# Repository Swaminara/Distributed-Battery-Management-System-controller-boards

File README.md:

# Distributed-Battery-Management-System-controller-boards

This repository contains the hardware design files of the cell-level controller boards of a distributed Battery Management System.

The boards are designed using Easily Applicable Graphical Layout Editor (EAGLE) 7.1.0 for Windows. However, they can be viewed and edited using other versions also. 

A journal paper explaining the individual modules of the cell-level controller is under review and will be soon updated to this repository. 

This repository is protected under the MIT license as attached in the repository.

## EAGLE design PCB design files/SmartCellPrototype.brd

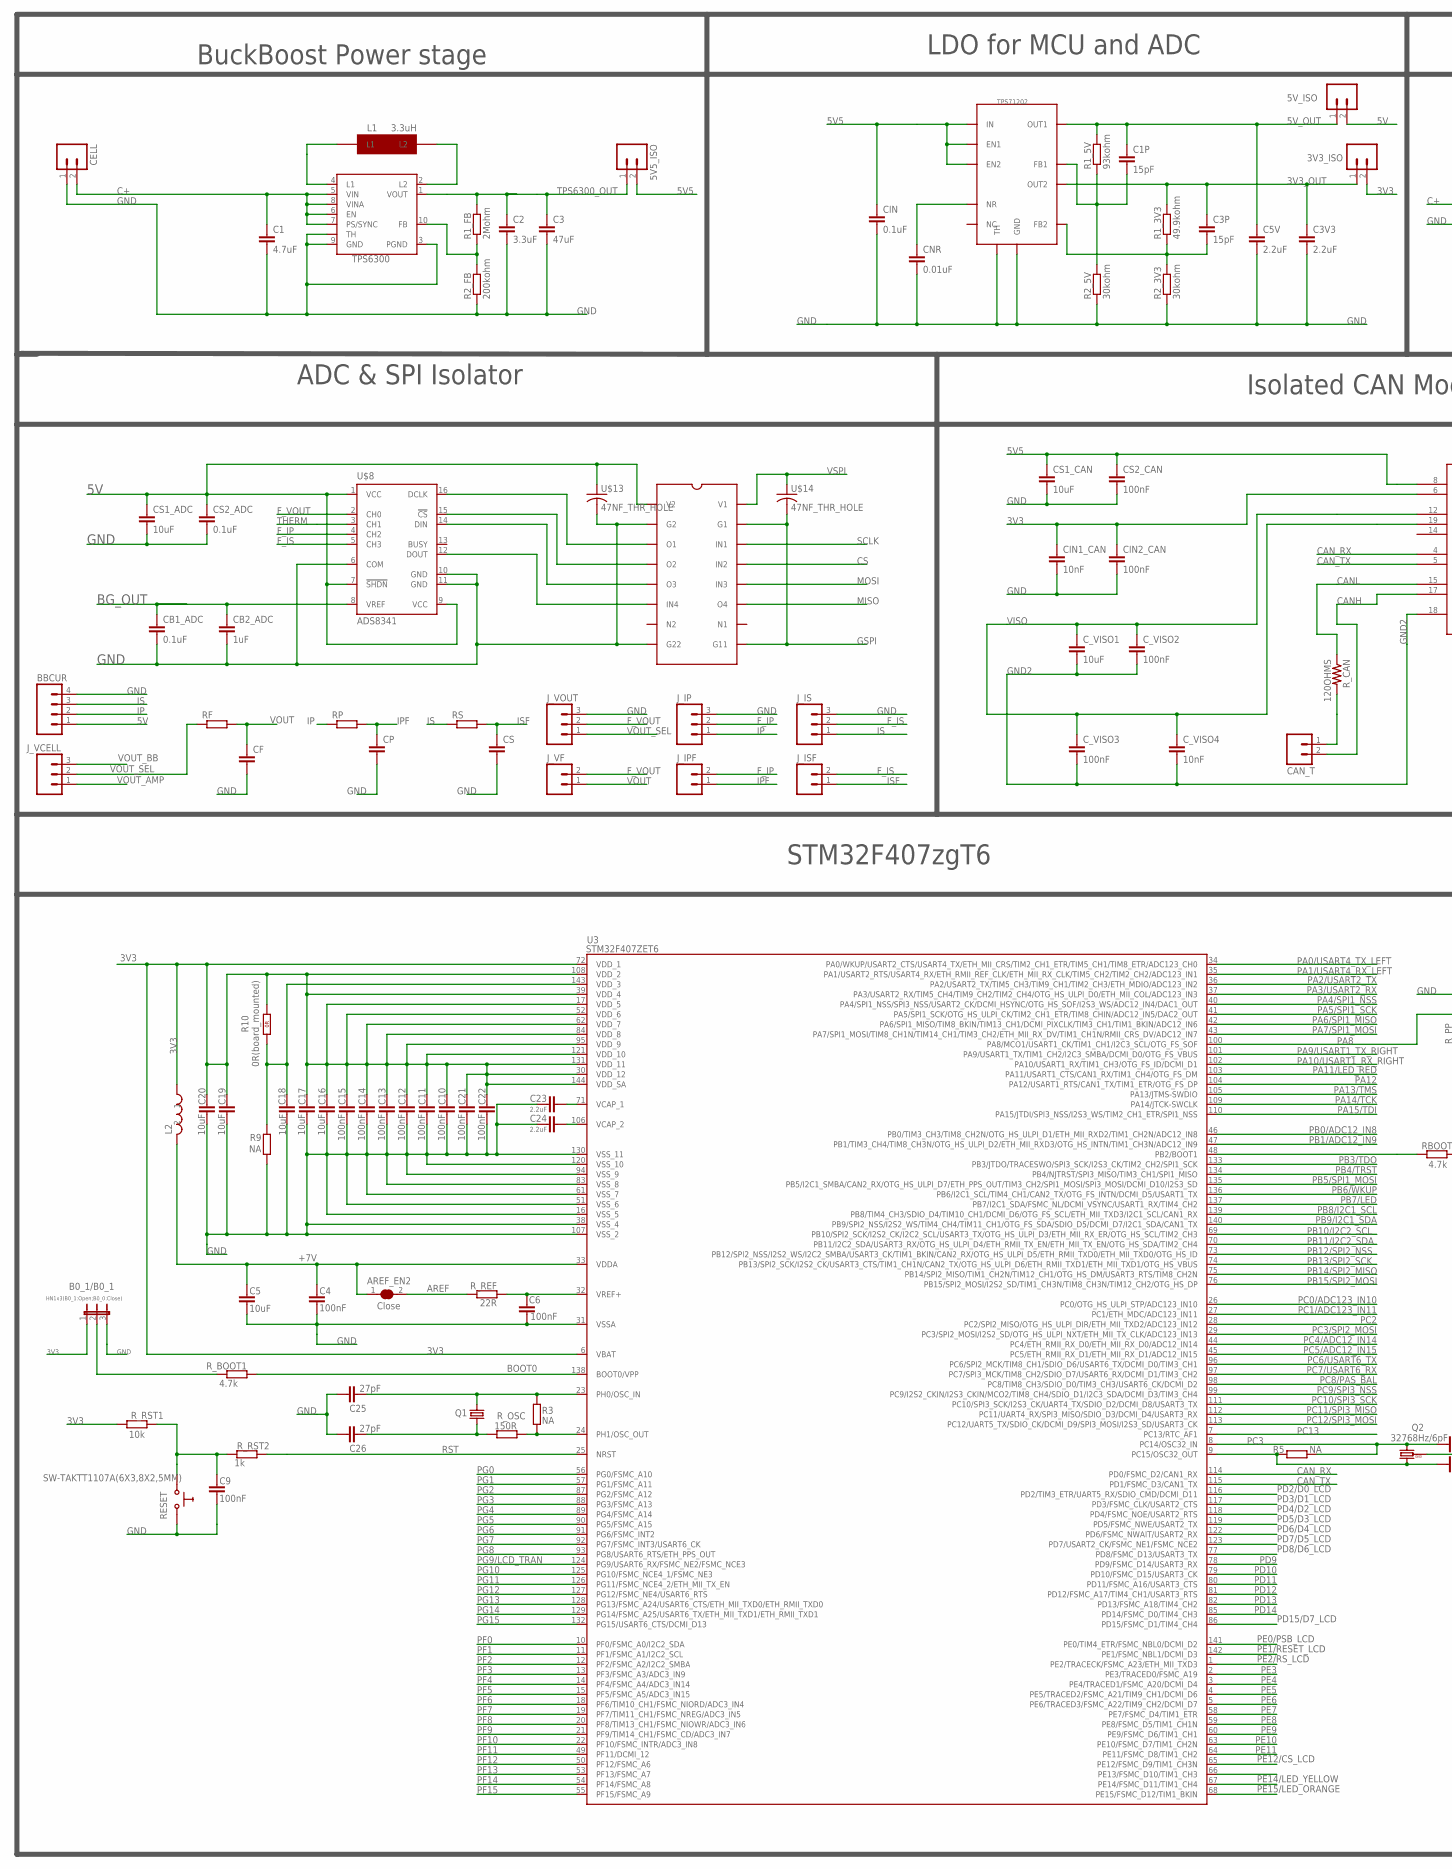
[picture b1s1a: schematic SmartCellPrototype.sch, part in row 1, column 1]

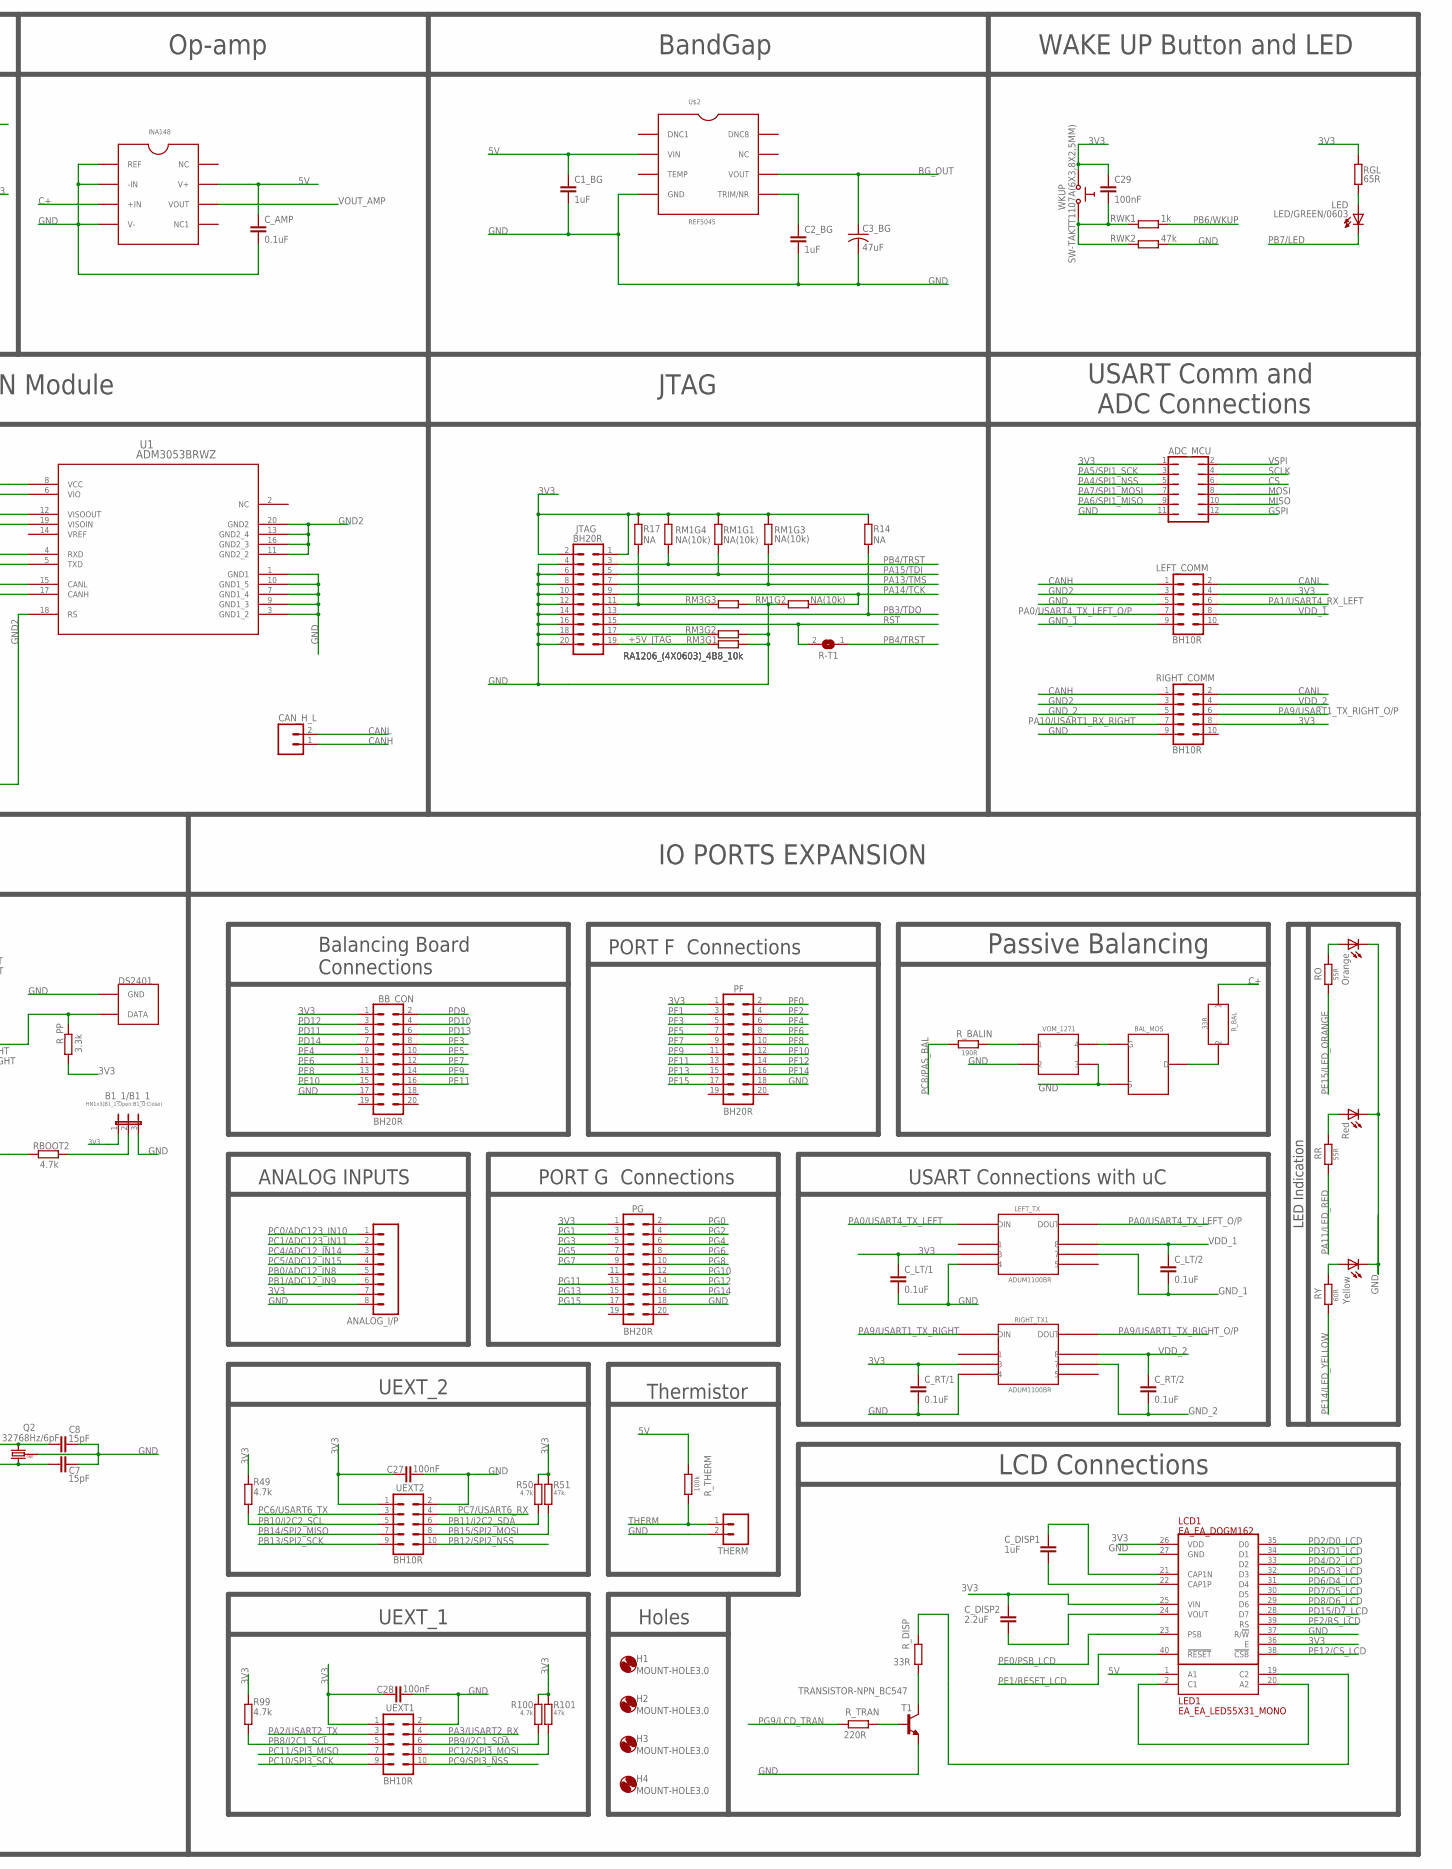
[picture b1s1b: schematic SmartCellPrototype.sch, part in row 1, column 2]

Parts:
3V3_ISO, 5V5_ISO, 5V_ISO: M02PTH; 1X02
ADC_MCU: JP6Q
ANALOG_I/P: M081X08; 1X08
AREF_EN2: Close; SJ_1_SMALLER_CLOSE
B0_1/B0_1: HN1x3(B0_1:Open;B0_0:Close); JP2
B1_1/B1_1: HN1x3(B1_1:Open;B1_0:Close); JP2
BAL_MOS: BAL_MOS
BBCUR: M04PTH; 1X04
BB_CON: BH20R
C1: 4.7uF; C0603
C1P, C3P, C7, C8: 15pF; C0603
C1_BG, C2_BG: 1uF; C0603
C2: 3.3uF; C0603
C3: 47uF; C0805
C3V3, C5V, C23, C24: 2.2uF; C0603
C3_BG: 47uF; C3_BG
C4, C6, C9, C10, C11, C12, C13, C14, C15, C21, C22, C27, C28: 100nF; C0603
C5, C16, C17, C18, C19, C20: 10uF; C0603
C25, C26: 27pF; C0603
C29: 100nF; C0805
CAN_H_L: M02PTH; 1X02
CAN_T: M02PTH; 1X02
CB1_ADC: 0.1uF; C0603
CB2_ADC: 1uF; C0603
CELL: M023.5MM; SCREWTERMINAL-3.5MM-2
CF: C-EUC0603; C0603
CIN: 0.1uF; C0603
CIN1_CAN: 10nF; C0603
CIN2_CAN: 100nF; C0603
CNR: 0.01uF; C0603
CP: C-EUC0603; C0603
CS: C-EUC0603; C0603
CS1_ADC, CS1_CAN: 10uF; C0603
CS2_ADC: 0.1uF; C0603
CS2_CAN: 100nF; C0603
C_AMP: 0.1uF; C0603
C_DISP1: 1uF; C0603
C_DISP2: 2.2uF; C0603
C_LT/1, C_LT/2: 0.1uF; C0603
C_RT/1, C_RT/2: 0.1uF; C0603
C_VISO1: 10uF; C0603
C_VISO2, C_VISO3: 100nF; C0603
C_VISO4: 10nF; C0603
DS2401: DS2401
H1, H2, H3, H4: MOUNT-HOLE3.0; 3,0
HCPL092J-00E: HCPL902
IC1: TPS6300; DRC-S-PVSON-N10
INA148: INA148
JTAG: BH20R
J_IP: M03PTH; 1X03
J_IPF: M02PTH; 1X02
J_IS: M03PTH; 1X03
J_ISF: M02PTH; 1X02
J_VCELL: M03PTH; 1X03
J_VF: M02PTH; 1X02
J_VOUT: M03PTH; 1X03
L1: 3.3uH; IND_COILCRAFT3.3UH
L2: FERRITE_BEAD
LCD1: EA_EA_DOGM162; EA_EA_DOGM
LED: LED/GREEN/0603; LED-0603
LED1: EA_EA_LED55X31_MONO; EA_EA_LED55X31
LEFT_COMM: BH10R
LEFT_TX: ADUM1100BR; R_8
PF: BH20R
PG: BH20R
Q1: HC49/S2; HC49/SMD2
Q2: 32768Hz/6pF; TC26H_3_REPAIR_SMD
R1_3V3: 49.9kohm; R0603
R1_5V: 93kohm; R0603
R1_FB: 2Mohm; R0603
R2_3V3, R2_5V: 30kohm; R0603
R2_FB: 200kohm; R0603
R3, R5, R9, R14, R17: NA; R0603
R10: 0R(board_mounted); 0603_0R
R49, R50, R99, R100: 4.7k; R0603
R51, R101: 47k; R0603
R-T1: Open; SJ_1_SMALLER
RBOOT2: 4.7k; R0603
RESET: SW-TAKTT1107A(6X3,8X2,5MM); WS-TAKT_6X3.5_SMD_NOCREAM
RF: R-EU_R0603; R0603
RGL: 65R; R0603_5MIL_DWS
RIGHT_COMM: BH10R
RIGHT_TX1: ADUM1100BR; R_8
RM1: NA(10k); R_MATRIX_4
RM3: RA1206_(4X0603)_4B8_10k; R_MATRIX_4
RO: 55R; R0603
RP: R-EU_R0603; R0603
RR: 55R; R0603
RS: R-EU_R0603; R0603
RWK1: 1k; R0603_5MIL_DWS
RWK2: 47k; R0603_5MIL_DWS
RY: 60R; R0603
R_BAL: 33R; R_BAL
R_BALIN: 190R; R0603
R_BOOT1: 4.7k; R0603
R_CAN: 120OHMS; 120OHM
R_DISP: 33R; R0603
R_OSC: 150R; R0603
R_PP: 3.3k; R0603
R_REF: 22R; R0603
R_RST1: 10k; R0603
R_RST2: 1k; R0603
R_THERM: 100k; R0603
R_TRAN: 220R; R0603
T1: TRANSISTOR-NPN_BC547; TRANSISTOR-NPN_TO92
THERM: M02JST-PTH-2; JST-2-PTH
U1: ADM3053BRWZ; RW_20
U3: STM32F407ZET6; LQFP144
U$1: TPS71202; TPS71202_LDO_ADC_MCU
U$2: REF5045; REF5045_BG
U$3: Yellow; LED_0805
U$4: Red; LED_0805
U$5: Orange; LED_0805
U$8: ADS8341
U$13, U$14: 47NF_THR_HOLE
UEXT1, UEXT2: BH10R
VOM_1271: VOM1271
WKUP: SW-TAKTT1107A(6X3,8X2,5MM); WS-TAKT_6X3.5_SMD_NOCREAM

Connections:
3V3: 3V3_ISO.2, ADC_MCU.1, ANALOG_I/P.7, B0_1/B0_1.1, B1_1/B1_1.1, BB_CON.1, C10.2, C11.2, C12.2, C13.2, C14.2, C15.2, C16.2, C17.2, C19.2, C20.2, C21.2, C22.2, C27.2, C28.2, C29.2, CIN1_CAN.1, CIN2_CAN.1, C_DISP2.1, C_LT/1.1, C_RT/1.1, JTAG.1, JTAG.2, L2.1, LCD1.25 (VIN), LCD1.26 (VDD), LCD1.36 (E), LEFT_COMM.4, LEFT_TX.3, PF.1, PG.1, R10.2 (1.2), R14.2, R17.2, R49.2, R50.2, R51.2, R99.2, R100.2, R101.2, RGL.2, RIGHT_COMM.8, RIGHT_TX1.3, RM1.1.2 (2), RM1.3.2 (2), RM1.4.2 (2), R_PP.1, R_RST1.2, U1.6 (VIO), U3.6 (VBAT), U3.17 (VDD_5), U3.30 (VDD_12), U3.39 (VDD_4), U3.52 (VDD_6), U3.62 (VDD_7), U3.72 (VDD_1), U3.84 (VDD_8), U3.95 (VDD_9), U3.108 (VDD_2), U3.121 (VDD_10), U3.131 (VDD_11), U3.144 (VDD_SA), UEXT1.1, UEXT2.1, WKUP.P$1 (0)
3V3_OUT: 3V3_ISO.1, C3P.1, C3V3.1, R1_3V3.2, U$1.4 (OUT2)
5V: 5V_ISO.2, BBCUR.1, C1_BG.1, CS1_ADC.1, CS2_ADC.1, C_AMP.1, HCPL092J-00E.V2, INA148.V+, LED1.1 (A1), R_THERM.2, U$2.VIN, U$8.1 (VCC), U$8.7 (!SHDN), U$8.9 (VCC), U$13.1
5V5: 5V5_ISO.2, CIN.1, CS1_CAN.1, CS2_CAN.1, U1.8 (VCC), U$1.1 (IN), U$1.8 (EN2), U$1.10 (EN1)
5V_OUT: 5V_ISO.1, C1P.1, C5V.1, R1_5V.2, U$1.3 (OUT1)
+5V_JTAG: JTAG.19, RM3.1.1 (1)
+7V: AREF_EN2.1, C4.2, C5.1, L2.2, U3.33 (VDDA)
AREF: AREF_EN2.2, R_REF.1
BG_OUT: C3_BG.+, CB1_ADC.1, CB2_ADC.1, U$2.VOUT, U$8.8 (VREF)
BOOT0: R_BOOT1.1, U3.138 (BOOT0/VPP)
C+: C1.1, CELL.2, IC1.5 (VIN), IC1.6 (EN), IC1.7 (PS/SYNC), IC1.8 (VINA), INA148.+IN, R_BAL.1
CANH: CAN_H_L.1, CAN_T.2, LEFT_COMM.1, RIGHT_COMM.1, U1.17 (CANH)
CANL: CAN_H_L.2, LEFT_COMM.2, RIGHT_COMM.2, R_CAN.1, U1.15 (CANL)
CAN_RX: U1.4 (RXD), U3.114 (PD0/FSMC_D2/CAN1_RX)
CAN_TX: U1.5 (TXD), U3.115 (PD1/FSMC_D3/CAN1_TX)
CS: ADC_MCU.6, HCPL092J-00E.IN2
F_IP: J_IP.2, J_IPF.2, U$8.4 (CH2)
F_IS: J_IS.2, J_ISF.2, U$8.5 (CH3)
F_VOUT: J_VF.2, J_VOUT.2, U$8.2 (CH0)
GND: ADC_MCU.11, ANALOG_I/P.8, B0_1/B0_1.3, B1_1/B1_1.3, BAL_MOS.S, BBCUR.4, BB_CON.17, C1.2, C1_BG.2, C2.2, C2_BG.2, C3.2, C3V3.2, C3_BG.-, C4.1, C5.2, C5V.2, C6.1, C7.2, C8.2, C9.1, C10.1, C11.1, C12.1, C13.1, C14.1, C15.1, C16.1, C17.1, C18.1, C19.1, C20.1, C21.1, C22.1, C23.1, C24.1, C25.2, C26.2, C27.1, C28.1, CB1_ADC.2, CB2_ADC.2, CELL.1, CF.2, CIN.2, CIN1_CAN.2, CIN2_CAN.2, CNR.2, CP.2, CS.2, CS1_ADC.2, CS1_CAN.2, CS2_ADC.2, CS2_CAN.2, C_AMP.2, C_LT/1.2, C_RT/1.2, DS2401.GND, HCPL092J-00E.G2, HCPL092J-00E.G22, IC1.3 (PGND), IC1.9 (GND), IC1.TH, INA148.-IN, INA148.REF, INA148.V-, JTAG.4, JTAG.6, JTAG.8, JTAG.10, JTAG.12, JTAG.14, JTAG.16, JTAG.18, JTAG.20, J_IP.3, J_IS.3, J_VOUT.3, LCD1.27 (GND), LCD1.37 (R/!W!), LEFT_COMM.5, LEFT_TX.4, PF.18, PG.18, Q2.GND, R2_3V3.1, R2_5V.1, R2_FB.1, R9.2, RESET.P$2 (1), RIGHT_COMM.9, RIGHT_TX1.4, RM1.2.1 (1), RM3.1.2 (2), RM3.2.2 (2), RM3.3.2 (2), RWK2.1, T1.1 (E), THERM.2, U1.1 (GND1), U1.3 (GND1_2), U1.7 (GND1_4), U1.9 (GND1_3), U1.10 (GND1_5), U3.16 (VSS_5), U3.31 (VSSA), U3.38 (VSS_4), U3.51 (VSS_6), U3.61 (VSS_7), U3.83 (VSS_8), U3.94 (VSS_9), U3.107 (VSS_2), U3.120 (VSS_10), U3.130 (VSS_11), U$1.5 (GND), U$1.TH, U$2.GND, U$3.K (C), U$4.K (C), U$5.K (C), U$8.6 (COM), U$8.10 (GND), U$8.11 (GND), U$13.2, UEXT1.2, UEXT2.2, VOM_1271.2, VOM_1271.3
GND2: C_VISO1.2, C_VISO2.2, C_VISO3.2, C_VISO4.2, LEFT_COMM.3, RIGHT_COMM.3, U1.11 (GND2_2), U1.13 (GND2_4), U1.16 (GND2_3), U1.18 (RS), U1.20 (GND2)
GND_1: C_LT/2.2, LEFT_COMM.9, LEFT_TX.7
GND_2: C_RT/2.2, RIGHT_COMM.5, RIGHT_TX1.7
GSPI: ADC_MCU.12, HCPL092J-00E.G1, HCPL092J-00E.G11, U$14.2
IP: BBCUR.2, J_IP.1, RP.1
IPF: CP.1, J_IPF.1, RP.2
IS: BBCUR.3, J_IS.1, RS.1
ISF: CS.1, J_ISF.1, RS.2
MISO: ADC_MCU.10, HCPL092J-00E.OUT4 (O4)
MOSI: ADC_MCU.8, HCPL092J-00E.IN3
unnamed: IC1.4 (L1), L1.L1
unnamed: IC1.2 (L2), L1.L2
unnamed: CAN_T.1, R_CAN.2
unnamed: C25.1, Q1.1, R3.2, U3.23 (PH0/OSC_IN)
unnamed: IC1.10 (FB), R1_FB.1, R2_FB.2
unnamed: CNR.1, U$1.6 (NR)
unnamed: C3P.2, R1_3V3.1, R2_3V3.2, U$1.7 (FB2)
unnamed: R3.1, R_OSC.2, U3.24 (PH1/OSC_OUT)
unnamed: C2_BG.1, U$2.TRIM/NR
unnamed: C1P.2, R1_5V.1, R2_5V.2, U$1.9 (FB1)
unnamed: B0_1/B0_1.2, R_BOOT1.2
unnamed: C9.2, RESET.P$1 (0), R_RST1.1, R_RST2.2
unnamed: LED.A, RGL.1
unnamed: C26.1, Q1.2, R_OSC.1
unnamed: BAL_MOS.D, R_BAL.2
unnamed: BAL_MOS.G, VOM_1271.4
unnamed: C23.2, U3.71 (VCAP_1)
unnamed: RY.1, U$3.A
unnamed: HCPL092J-00E.IN4, U$8.12 (DOUT)
unnamed: HCPL092J-00E.OUT3 (O3), U$8.14 (DIN)
unnamed: HCPL092J-00E.OUT2 (O2), U$8.15 (!CS)
unnamed: HCPL092J-00E.OUT1 (O1), U$8.16 (DCLK)
unnamed: C_DISP1.1, LCD1.21 (CAP1N)
unnamed: C29.1, RWK1.1, RWK2.2, WKUP.P$2 (1)
unnamed: RR.1, U$4.A
unnamed: RBOOT2.1, U3.48 (PB2/BOOT1)
unnamed: RO.1, U$5.A
unnamed: C24.2, U3.106 (VCAP_2)
unnamed: C_DISP1.2, LCD1.22 (CAP1P)
unnamed: R_BALIN.2, VOM_1271.1
unnamed: C_DISP2.2, LCD1.24 (VOUT)
unnamed: LED1.2 (C1), LED1.20 (A2)
unnamed: C18.2, R9.1, R10.1 (1.1), U3.143 (VDD_3)
unnamed: B1_1/B1_1.2, RBOOT2.2
unnamed: JTAG.11, R17.1, RM3.3.1 (1)
unnamed: JTAG.17, RM3.2.1 (1)
unnamed: LED1.19 (C2), R_DISP.2
unnamed: R_DISP.1, T1.3 (C)
unnamed: R_TRAN.1, T1.2 (B)
PA0/USART4_TX_LEFT: LEFT_TX.2 (DIN), U3.34 (PA0/WKUP/USART2_CTS/USART4_TX/ETH_MII_C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)
PA0/USART4_TX_LEFT_O/P: LEFT_COMM.7, LEFT_TX.6 (DOUT)
PA1/USART4_RX_LEFT: LEFT_COMM.6, U3.35 (PA1/USART2_RTS/USART4_RX/ETH_RMII_REF_C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)
PA2/USART2_TX: U3.36 (PA2/USART2_TX/TIM5_CH3/TIM9_CH1/TIM2_CH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), UEXT1.3
PA3/USART2_RX: U3.37 (PA3/USART2_RX/TIM5_CH4/TIM9_CH2/TIM2_CH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), UEXT1.4
PA4/SPI1_NSS: ADC_MCU.5, U3.40 (PA4/SPI1_NSS/SPI3_NSS/USART2_CK/DCMI_HS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)
PA5/SPI1_SCK: ADC_MCU.3, U3.41 (PA5/SPI1_SCK/OTG_HS_ULPI_CK/TIM2_CH1_ET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)
PA6/SPI1_MISO: ADC_MCU.9, U3.42 (PA6/SPI1_MISO/TIM8_BKIN/TIM13_CH1/DCMI_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)
PA7/SPI1_MOSI: ADC_MCU.7, U3.43 (PA7/SPI1_MOSI/TIM8_CH1N/TIM14_CH1/TIM3_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)
PA8: DS2401.DATA, R_PP.2, U3.100 (PA8/MCO1/USART1_CK/TIM1_CH1/I2C3_SCL/OT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)
PA9/USART1_TX_RIGHT: RIGHT_TX1.2 (DIN), U3.101 (PA9/USART1_TX/TIM1_CH2/I2C3_SMBA/DCMI_D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)
PA9/USART1_TX_RIGHT_O/P: RIGHT_COMM.6, RIGHT_TX1.6 (DOUT)
PA10/USART1_RX_RIGHT: RIGHT_COMM.7, U3.102 (PA10/USART1_RX/TIM1_CH3/OTG_FS_ID/DCMI_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)
PA11/LED_RED: RR.2, U3.103 (PA11/USART1_CTS/CAN1_RX/TIM1_CH4/OTG_FS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)
PA12: U3.104 (PA12/USART1_RTS/CAN1_TX/TIM1_ETR/OTG_FS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)
PA13/TMS: JTAG.7, RM1.3.1 (1), U3.105 (PA13/JTMS-SWDIO)
PA14/TCK: JTAG.9, RM1.2.2 (2), U3.109 (PA14/JTCK-SWCLK)
PA15/TDI: JTAG.5, RM1.1.1 (1), U3.110 (PA15/JTDI/SPI3_NSS/I2S3_WS/TIM2_CH1_ETR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)
PB0/ADC12_IN8: ANALOG_I/P.5, U3.46 (PB0/TIM3_CH3/TIM8_CH2N/OTG_HS_ULPI_D1/E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)
PB1/ADC12_IN9: ANALOG_I/P.6, U3.47 (PB1/TIM3_CH4/TIM8_CH3N/OTG_HS_ULPI_D2/E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)
PB3/TDO: JTAG.13, R14.1, U3.133 (PB3/JTDO/TRACESWO/SPI3_SCK/I2S3_CK/TIM2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)
PB4/TRST: JTAG.3, R-T1.1, RM1.4.1 (1), U3.134 (PB4/NJTRST/SPI3_MISO/TIM3_CH1/SPI1_MISO)
PB5/SPI1_MOSI: U3.135 (PB5/I2C1_SMBA/CAN2_RX/OTG_HS_ULPI_D7/ET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)
PB6/WKUP: RWK1.2, U3.136 (PB6/I2C1_SCL/TIM4_CH1/CAN2_TX/OTG_FS_IN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)
PB7/LED: LED.C, U3.137 (PB7/I2C1_SDA/FSMC_NL/DCMI_VSYNC/USART1_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)
PB8/I2C1_SCL: R99.1, U3.139 (PB8/TIM4_CH3/SDIO_D4/TIM10_CH1/DCMI_D6/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), UEXT1.5
PB9/I2C1_SDA: R100.1, U3.140 (PB9/SPI2_NSS/I2S2_WS/TIM4_CH4/TIM11_CH1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), UEXT1.6
PB10/I2C2_SCL: R49.1, U3.69 (PB10/SPI2_SCK/I2S2_CK/I2C2_SCL/USART3_T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), UEXT2.5
PB11/I2C2_SDA: R50.1, U3.70 (PB11/I2C2_SDA/USART3_RX/OTG_HS_ULPI_D4/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), UEXT2.6
PB12/SPI2_NSS: U3.73 (PB12/SPI2_NSS/I2S2_WS/I2C2_SMBA/USART3_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), UEXT2.10
PB13/SPI2_SCK: U3.74 (PB13/SPI2_SCK/I2S2_CK/USART3_CTS/TIM1_C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), UEXT2.9
PB14/SPI2_MISO: U3.75 (PB14/SPI2_MISO/TIM1_CH2N/TIM12_CH1/OTG_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), UEXT2.7
PB15/SPI2_MOSI: R51.1, U3.76 (PB15/SPI2_MOSI/I2S2_SD/TIM1_CH3N/TIM8_C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), UEXT2.8
PC0/ADC123_IN10: ANALOG_I/P.1, U3.26 (PC0/OTG_HS_ULPI_STP/ADC123_IN10)
PC1/ADC123_IN11: ANALOG_I/P.2, U3.27 (PC1/ETH_MDC/ADC123_IN11)
PC2: U3.28 (PC2/SPI2_MISO/OTG_HS_ULPI_DIR/ETH_MII_T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)
PC3: C8.1, Q2.2, R5.2, U3.8 (PC14/OSC32_IN)
PC3/SPI2_MOSI: U3.29 (PC3/SPI2_MOSI/I2S2_SD/OTG_HS_ULPI_NXT/E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)
PC4: C7.1, Q2.1, R5.1, U3.9 (PC15/OSC32_OUT)
PC4/ADC12_IN14: ANALOG_I/P.3, U3.44 (PC4/ETH_RMII_RX_D0/ETH_MII_RX_D0/ADC12_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)
PC5/ADC12_IN15: ANALOG_I/P.4, U3.45 (PC5/ETH_RMII_RX_D1/ETH_MII_RX_D1/ADC12_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)
PC6/USART6_TX: U3.96 (PC6/SPI2_MCK/TIM8_CH1/SDIO_D6/USART6_TX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), UEXT2.3
PC7/USART6_RX: U3.97 (PC7/SPI3_MCK/TIM8_CH2/SDIO_D7/USART6_RX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), UEXT2.4
PC8/PAS_BAL: R_BALIN.1, U3.98 (PC8/TIM8_CH3/SDIO_D0/TIM3_CH3/USART6_CK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)
PC9/SPI3_NSS: U3.99 (PC9/I2S2_CKIN/I2S3_CKIN/MCO2/TIM8_CH4/S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), UEXT1.10
PC10/SPI3_SCK: U3.111 (PC10/SPI3_SCK/I2S3_CK/UART4_TX/SDIO_D2/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), UEXT1.9
PC11/SPI3_MISO: U3.112 (PC11/UART4_RX/SPI3_MISO/SDIO_D3/DCMI_D4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), UEXT1.7
PC12/SPI3_MOSI: R101.1, U3.113 (PC12/UART5_TX/SDIO_CK/DCMI_D9/SPI3_MOSI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), UEXT1.8
PC13: U3.7 (PC13/RTC_AF1)
PD2/D0_LCD: LCD1.35 (D0), U3.116 (PD2/TIM3_ETR/UART5_RX/SDIO_CMD/DCMI_D11)
PD3/D1_LCD: LCD1.34 (D1), U3.117 (PD3/FSMC_CLK/USART2_CTS)
PD4/D2_LCD: LCD1.33 (D2), U3.118 (PD4/FSMC_NOE/USART2_RTS)
PD5/D3_LCD: LCD1.32 (D3), U3.119 (PD5/FSMC_NWE/USART2_TX)
PD6/D4_LCD: LCD1.31 (D4), U3.122 (PD6/FSMC_NWAIT/USART2_RX)
PD7/D5_LCD: LCD1.30 (D5), U3.123 (PD7/USART2_CK/FSMC_NE1/FSMC_NCE2)
PD8/D6_LCD: LCD1.29 (D6), U3.77 (PD8/FSMC_D13/USART3_TX)
PD9: BB_CON.2, U3.78 (PD9/FSMC_D14/USART3_RX)
PD10: BB_CON.4, U3.79 (PD10/FSMC_D15/USART3_CK)
PD11: BB_CON.5, U3.80 (PD11/FSMC_A16/USART3_CTS)
PD12: BB_CON.3, U3.81 (PD12/FSMC_A17/TIM4_CH1/USART3_RTS)
PD13: BB_CON.6, U3.82 (PD13/FSMC_A18/TIM4_CH2)
PD14: BB_CON.7, U3.85 (PD14/FSMC_D0/TIM4_CH3)
PD15/D7_LCD: LCD1.28 (D7), U3.86 (PD15/FSMC_D1/TIM4_CH4)
PE0/PSB_LCD: LCD1.23 (PSB), U3.141 (PE0/TIM4_ETR/FSMC_NBL0/DCMI_D2)
PE1/RESET_LCD: LCD1.40 (!RESET!), U3.142 (PE1/FSMC_NBL1/DCMI_D3)
PE2/RS_LCD: LCD1.39 (RS), U3.1 (PE2/TRACECK/FSMC_A23/ETH_MII_TXD3)
PE3: BB_CON.8, U3.2 (PE3/TRACED0/FSMC_A19)
PE4: BB_CON.9, U3.3 (PE4/TRACED1/FSMC_A20/DCMI_D4)
PE5: BB_CON.10, U3.4 (PE5/TRACED2/FSMC_A21/TIM9_CH1/DCMI_D6)
PE6: BB_CON.11, U3.5 (PE6/TRACED3/FSMC_A22/TIM9_CH2/DCMI_D7)
PE7: BB_CON.12, U3.58 (PE7/FSMC_D4/TIM1_ETR)
PE8: BB_CON.13, U3.59 (PE8/FSMC_D5/TIM1_CH1N)
PE9: BB_CON.14, U3.60 (PE9/FSMC_D6/TIM1_CH1)
PE10: BB_CON.15, U3.63 (PE10/FSMC_D7/TIM1_CH2N)
PE11: BB_CON.16, U3.64 (PE11/FSMC_D8/TIM1_CH2)
PE12/CS_LCD: LCD1.38 (!CSB!), U3.65 (PE12/FSMC_D9/TIM1_CH3N)
PE14/LED_YELLOW: RY.2, U3.67 (PE14/FSMC_D11/TIM1_CH4)
PE15/LED_ORANGE: RO.2, U3.68 (PE15/FSMC_D12/TIM1_BKIN)
PF0: PF.2, U3.10 (PF0/FSMC_A0/I2C2_SDA)
PF1: PF.3, U3.11 (PF1/FSMC_A1/I2C2_SCL)
PF2: PF.4, U3.12 (PF2/FSMC_A2/I2C2_SMBA)
PF3: PF.5, U3.13 (PF3/FSMC_A3/ADC3_IN9)
PF4: PF.6, U3.14 (PF4/FSMC_A4/ADC3_IN14)
PF5: PF.7, U3.15 (PF5/FSMC_A5/ADC3_IN15)
PF6: PF.8, U3.18 (PF6/TIM10_CH1/FSMC_NIORD/ADC3_IN4)
PF7: PF.9, U3.19 (PF7/TIM11_CH1/FSMC_NREG/ADC3_IN5)
PF8: PF.10, U3.20 (PF8/TIM13_CH1/FSMC_NIOWR/ADC3_IN6)
PF9: PF.11, U3.21 (PF9/TIM14_CH1/FSMC_CD/ADC3_IN7)
PF10: PF.12, U3.22 (PF10/FSMC_INTR/ADC3_IN8)
PF11: PF.13, U3.49 (PF11/DCMI_12)
PF12: PF.14, U3.50 (PF12/FSMC_A6)
PF13: PF.15, U3.53 (PF13/FSMC_A7)
PF14: PF.16, U3.54 (PF14/FSMC_A8)
PF15: PF.17, U3.55 (PF15/FSMC_A9)
PG0: PG.2, U3.56 (PG0/FSMC_A10)
PG1: PG.3, U3.57 (PG1/FSMC_A11)
PG2: PG.4, U3.87 (PG2/FSMC_A12)
PG3: PG.5, U3.88 (PG3/FSMC_A13)
PG4: PG.6, U3.89 (PG4/FSMC_A14)
PG5: PG.7, U3.90 (PG5/FSMC_A15)
PG6: PG.8, U3.91 (PG6/FSMC_INT2)
PG7: PG.9, U3.92 (PG7/FSMC_INT3/USART6_CK)
PG8: PG.10, U3.93 (PG8/USART6_RTS/ETH_PPS_OUT)
PG9/LCD_TRAN: R_TRAN.2, U3.124 (PG9/USART6_RX/FSMC_NE2/FSMC_NCE3)
PG10: PG.12, U3.125 (PG10/FSMC_NCE4_1/FSMC_NE3)
PG11: PG.13, U3.126 (PG11/FSMC_NCE4_2/ETH_MII_TX_EN)
PG12: PG.14, U3.127 (PG12/FSMC_NE4/USART6_RTS)
PG13: PG.15, U3.128 (PG13/FSMC_A24/USART6_CTS/ETH_MII_TXD0/E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)
PG14: PG.16, U3.129 (PG14/FSMC_A25/USART6_TX/ETH_MII_TXD1/ET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)
PG15: PG.17, U3.132 (PG15/USART6_CTS/DCMI_D13)
RST: JTAG.15, R-T1.2, R_RST2.1, U3.25 (NRST)
SCLK: ADC_MCU.4, HCPL092J-00E.IN1
THERM: R_THERM.1, THERM.1, U$8.3 (CH1)
TPS6300_OUT: 5V5_ISO.1, C2.1, C3.1, IC1.1 (VOUT), R1_FB.2
VDD_1: C_LT/2.1, LEFT_COMM.8, LEFT_TX.8
VDD_2: C_RT/2.1, RIGHT_COMM.4, RIGHT_TX1.8
VISO: C_VISO1.1, C_VISO2.1, C_VISO3.1, C_VISO4.1, U1.12 (VISOOUT), U1.19 (VISOIN)
VOUT: CF.1, J_VF.1, RF.2
VOUT_AMP: INA148.VOUT, J_VCELL.1
VOUT_BB: J_VCELL.3
VOUT_SEL: J_VCELL.2, J_VOUT.1, RF.1
VREF+2: C6.2, R_REF.2, U3.32 (VREF+)
VSPI: ADC_MCU.2, HCPL092J-00E.V1, U$14.1

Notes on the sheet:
BuckBoost Power stage
LDO for MCU and ADC
Op-amp
BandGap
ADC & SPI Isolator
Isolated CAN Module
JTAG
IO PORTS EXPANSION
STM32F407zgT6
Balancing Board Connections
PORT F Connections
PORT G Connections
UEXT_2
UEXT_1
ANALOG INPUTS
WAKE UP Button and LED
Passive Balancing
USART Comm and ADC Connections
Thermistor
USART Connections with uC
LED Indication
LCD Connections
Holes

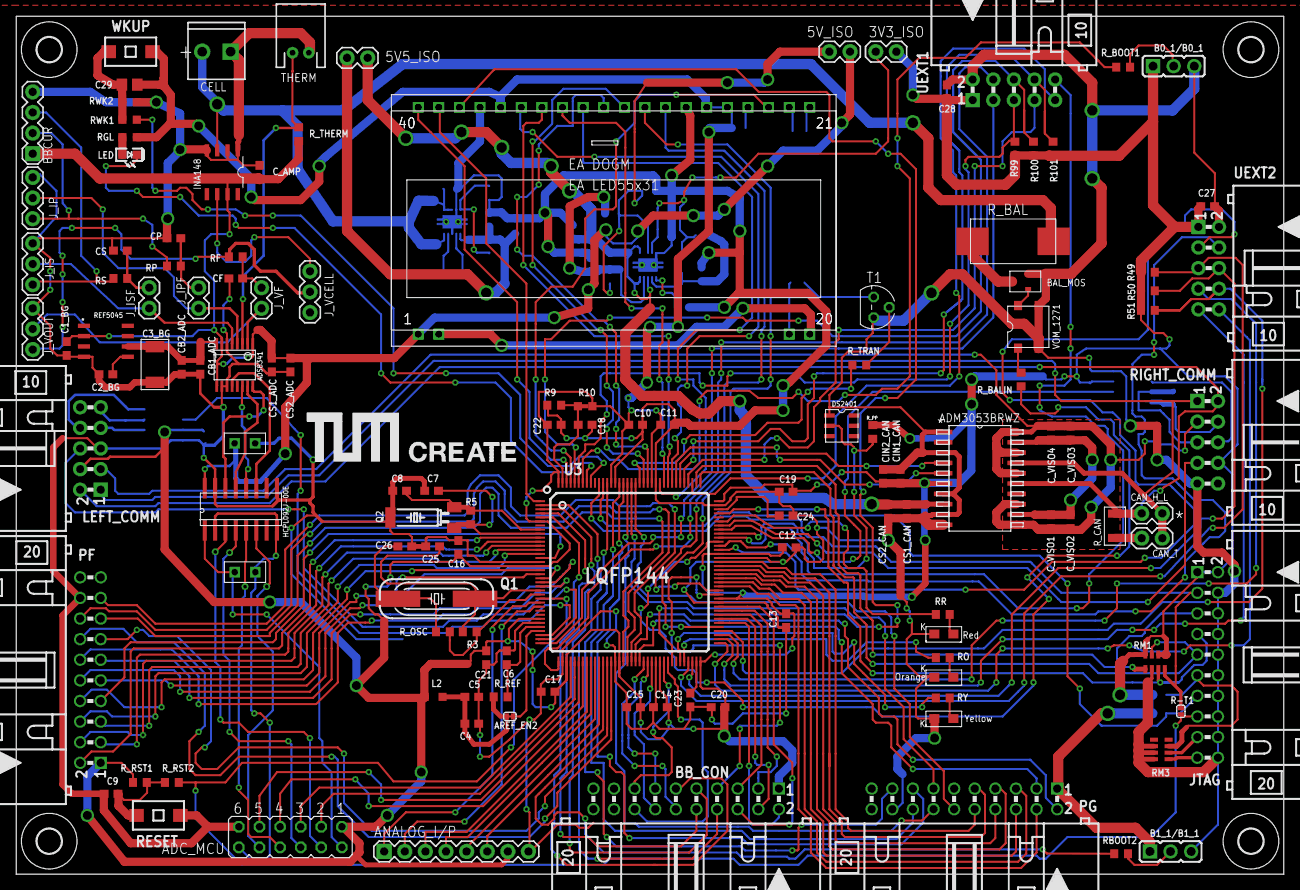
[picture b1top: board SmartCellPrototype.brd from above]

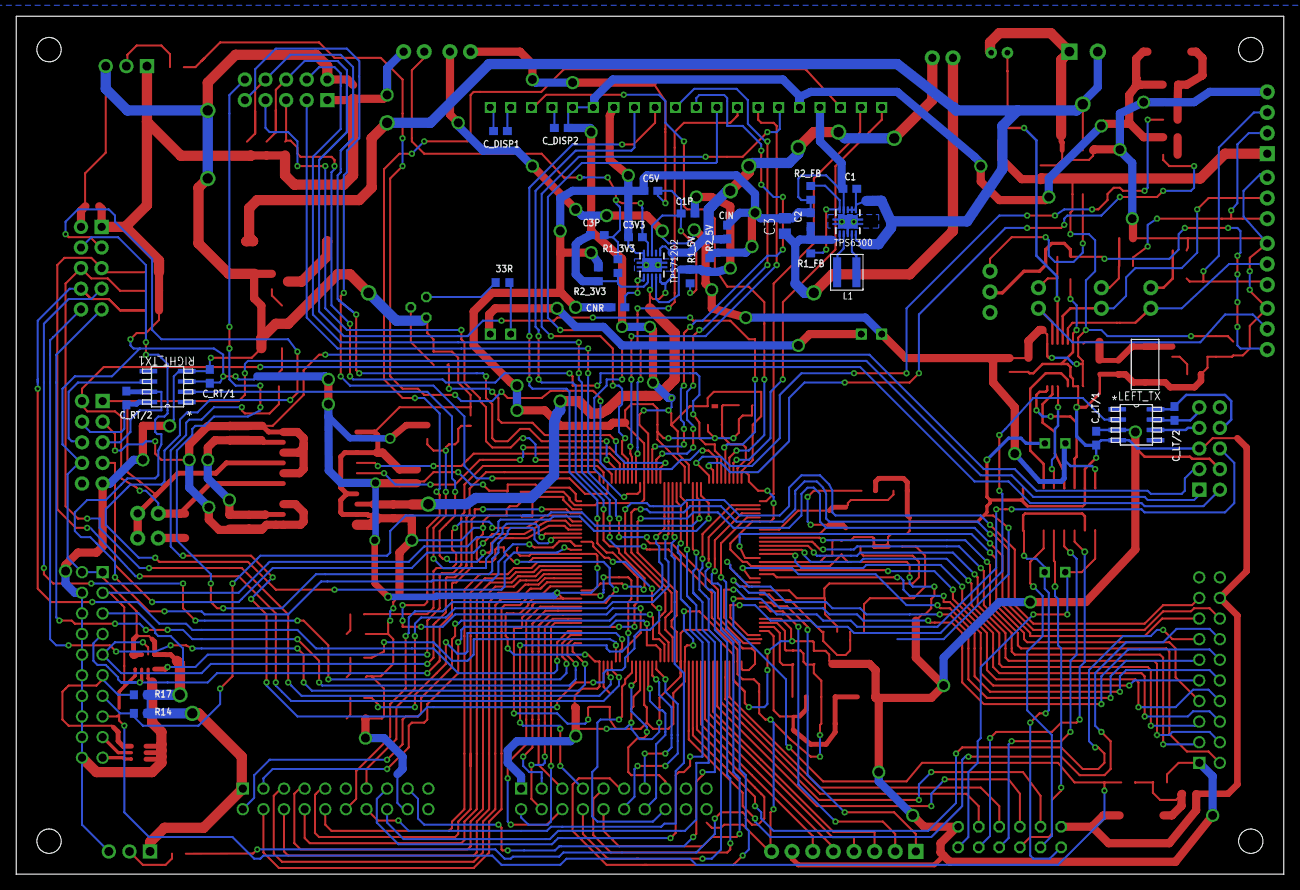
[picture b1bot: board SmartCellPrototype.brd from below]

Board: 2 copper layers, 156.2 x 105.7 mm, 164 parts (29 on the bottom side), 186 nets.

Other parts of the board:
U$6: BIGGER_LOGO

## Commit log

2016-02-19 Added author names in the license file and board design files to the repository.

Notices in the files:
parts and their libraries:
SparkFun-Connectors: Licensing: CC v3.0 Share-Alike You are welcome to use this library for commercial purposes.
